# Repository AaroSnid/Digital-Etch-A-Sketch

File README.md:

# Digital Etch-A-Sketch

The **Digital Etch-A-Sketch** is a portable recreation of the classic Etch-A-Sketch drawing toy, built around an STM32 microcontroller, a 3.5" TFT display, and  rotary encoders for drawing cursor control. This project's main features are the rotary encoder cursor control, realistic screen erase gesture, and selectable drawing thickness.

> **Status:** Major Firmware Version Finalized
> **Hardware Version:** Rev1

---

## Features

- **Freehand Drawing**
  - Pixel-accurate cursor control
  - Trailless travel / eraser function
  - Selectable drawing thickness and brightness control

- **Physical Controls**
  - Two rotary encoders for X/Y movement
  - Encoder pushbuttons to for system setting selection

- **Shake to Erase**
  - Accelerometer detect motion for realistic screen erase gesture 

- **Portable & Low Power**
  - Powered by 2× AA batteries or by USB-C port

---

## Bill of Materials (Summary)

| Item            | Part Number        | Qty | Notes |
|-----------------|--------------------|-----|-------|
| MCU             | STM32L433CCT6      | 1   | Main controller |
| Display         | 3.5" ILI9488 SPI   | 1   | 3.5" display |
| QSPI Flash      | For future expansion | 1   | Reserved for future use |
| 3-axis Accelerometer      | LIS3DTHR        | 1   | 3-axis velocity sensor |
| Rotary Encoder  | PEC11R-4215F-S0024 | 2   | User input |
| Battery Holder  | Adafruit 4194      | 1   | 2× AA |

---

## Hardware Subsystems

### Power Supply

- **Part:** Adafruit 4194
- **Input:** 2 × AA batteries (2.2–3.2 V)
- **Output:** 3.0 V 
- **Max Load:** ~400 mA
- **Purpose:** Powers the entire system from AA cells

---

### Microcontroller

- **Part:** STM32L433CCT3 / STM32L433CCT6  
- **Clock:** 80 MHz (internal)
- **Memory:**  
  - 256 KB Flash  
  - 64 KB RAM  

**Key Peripherals**

| Function         | Peripheral | Notes |
|------------------|------------|-------|
| Display          | SPI3       | Half-duplex, optimized for fast updates |
| Accelerometer    | SPI2, EXTI | Full-duplex |
| Flash memory     | Quad-SPI   | Memory-mapped reads |
| Rotary Encoders  | TIM1&2, EXTI | QEI mode with interrupts |
| Debug            | SWD        | DIO, CLK, NRST |

---

### Display

- **Type:** 3.5" TFT Display
- **Controller:** ILI9488
- **Interface:** Dedicated 4-wire SPI
- **Power:** 3.3 V
- **Frame Buffer:** Embedded GRAM
- **Update Modes:** Full and partial refresh
The screen is mounted to the board using the female pin headers on either side. The touchscreen functionality of the screen is not used, so the touchscreen pins are not conected.

---

### Storage

- **Part:** For future expansion
- **Capacity:** Reserved for future use
- **Interface:** Quad SPI (if added later)
- **Purpose:**
  - Potential animation frame storage
  - Potential configuration data

---

### Motion Sensor

- **Part:** LIS3DTHR
- **Interface:** SPI
- **Capabilities:** 3-axis accelerometer
- **Usage:**
  - Detect shake gesture for screen erase
  - Uses interrupts for main motion detection
  - SPI available as fallback

---

### Rotary Encoders

- **Quantity:** 2
- **Part:** PEC11R-4215F-S0024
- **Purpose:**
  - X-axis and Y-axis cursor movement
  - UI interaction via push buttons

**Connections**
- A/B channels → Timer QEI inputs
- Buttons → EXTI interrupts
- Hardware Pull-ups (open-drain behavior)

---

## Firmware Architecture

### Overview

The firmware runs inside of a state machine, easily allowing for the same user inputs to be used for different purposes.
The main loop runs (per iteration) a check for the screen erase, handles state change, and then enters the state machine section for currently selected action.
An external driver is used for the ILI9488 display, all other firmware is made by me.

---

## Debug & Firmware Update

- **Interface:** SWD
- **Exposed Pins:**  
  - SWDIO  
  - SWCLK  
  - NRST  
  - VCC + GND

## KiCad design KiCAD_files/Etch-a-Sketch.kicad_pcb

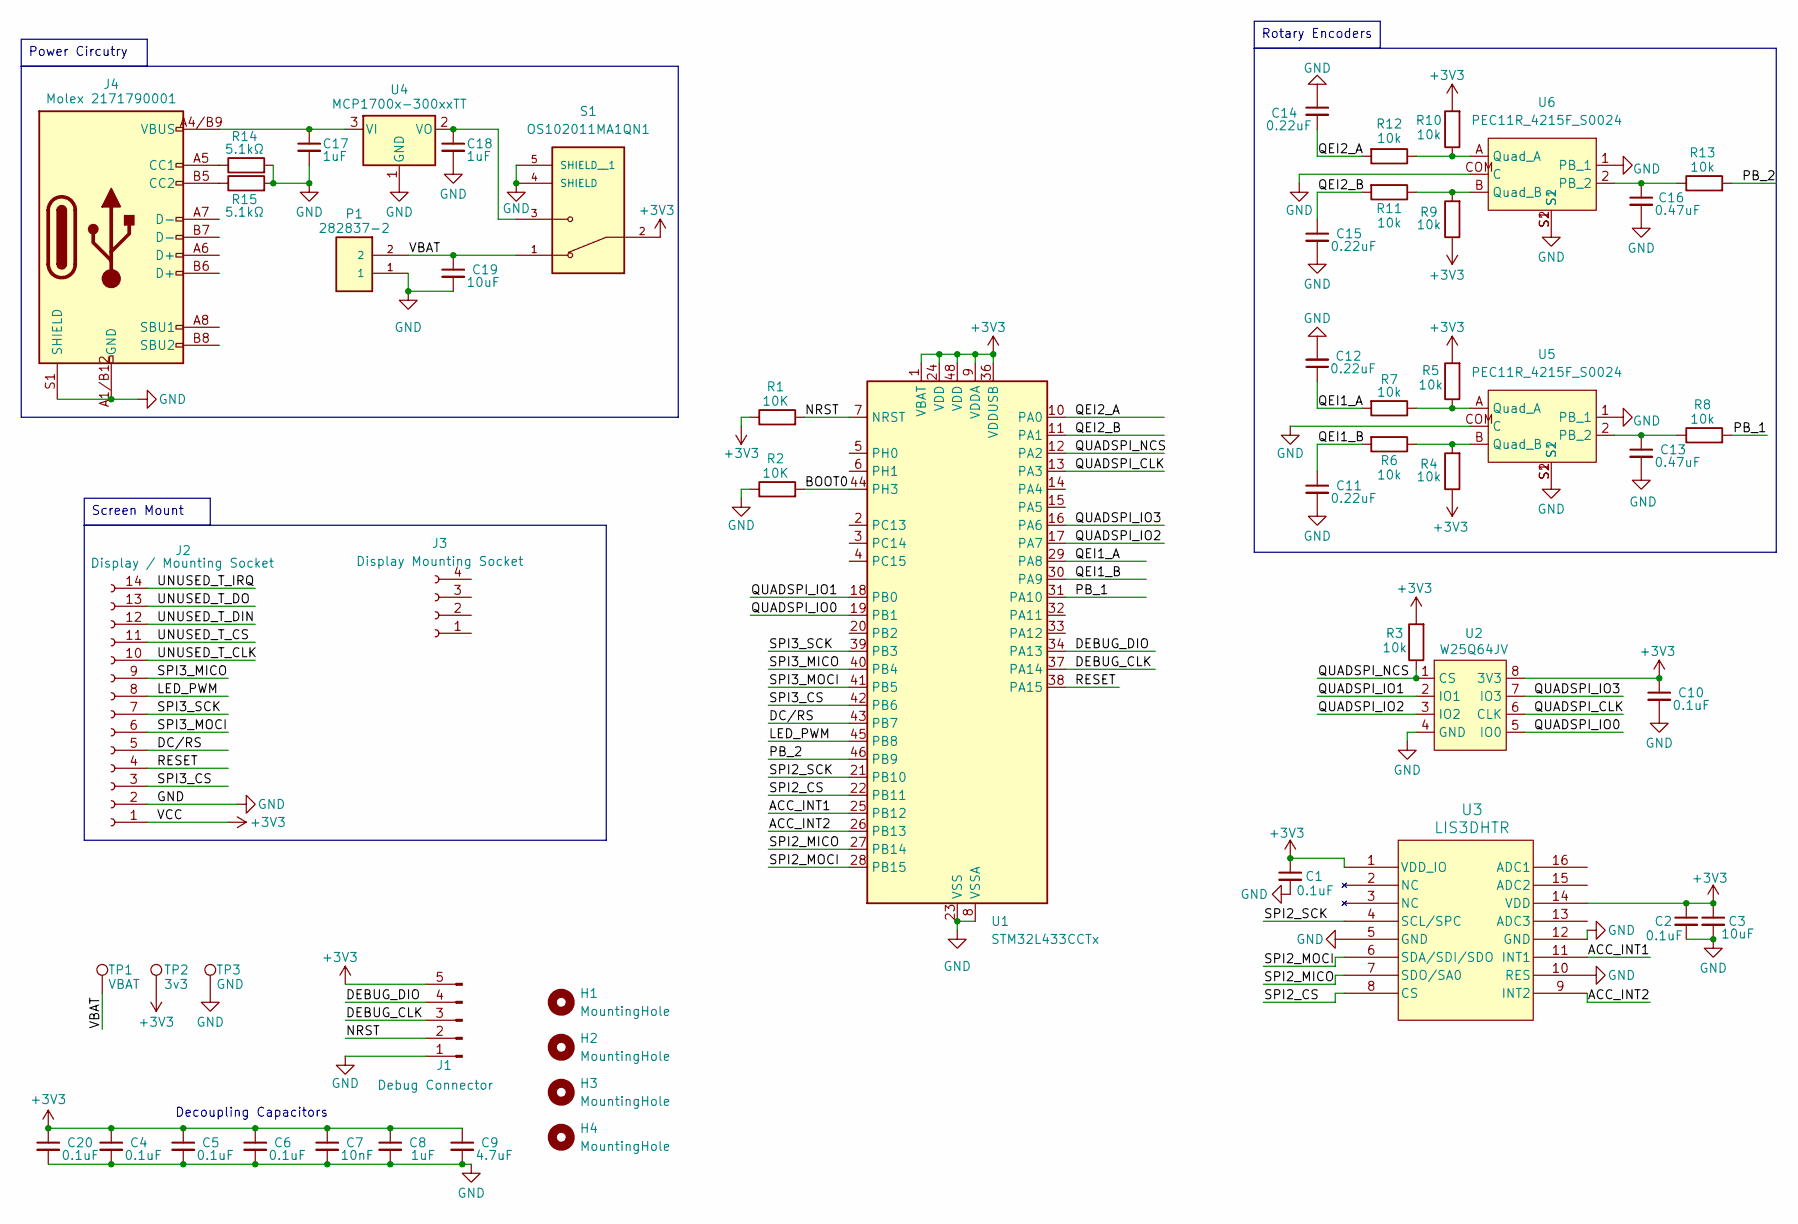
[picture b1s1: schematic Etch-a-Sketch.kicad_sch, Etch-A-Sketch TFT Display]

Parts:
C1, C2, C4, C5, C6, C10, C20: 0.1uF; C_0603_1608Metric
C3, C19: 10uF; C_0603_1608Metric
C7: 10nF; C_0603_1608Metric
C8, C17, C18: 1uF; C_0603_1608Metric
C9: 4.7uF; C_0603_1608Metric
C11, C12, C14, C15: 0.22uF; C_0603_1608Metric
C13, C16: 0.47uF; C_0603_1608Metric
H1, H2, H3, H4: MountingHole; ToolingHole_1.152mm
J1: Debug Connector; PinHeader_1x05_P2.54mm_Vertical
J2: Display / Mounting Socket; PinSocket_1x14_P2.54mm_Vertical
J3: Display Mounting Socket; PinSocket_1x04_P2.54mm_Vertical
J4: Molex 2171790001; 2171790001_MOL
P1: 282837-2; JST_PH_B2B-PH-K_1x02_P2.00mm_Vertical; PARTREV G3
R1, R2: 10K; R_0603_1608Metric
R3, R4, R5, R6, R7, R8, R9, R10, R11, R12, R13: 10k; R_0603_1608Metric
R14, R15: 5.1kΩ; R_0603_1608Metric
S1: OS102011MA1QN1; OS102011MA1QN1_CNK; PARTREV A
TP1: VBAT; TestPoint_Loop_D1.80mm_Drill1.0mm_Beaded
TP2: 3v3; TestPoint_Loop_D1.80mm_Drill1.0mm_Beaded
TP3: GND; TestPoint_Loop_D1.80mm_Drill1.0mm_Beaded
U1: STM32L433CCTx; LQFP-48_7x7mm_P0.5mm
U2: W25Q64JV; SOIC-8_5P28X5P28_WIN
U3: LIS3DHTR; LGA-16_3x3x1mm_STM
U4: MCP1700x-300xxTT; SOT-23
U5, U6: PEC11R_4215F_S0024; XDCR_PEC11R-4215F-S0024

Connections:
+3V3: C1.1, C2.1, C3.1, C4.1, C5.1, C6.1, C7.1, C8.1, C9.1, C10.1, C20.1, J1.5, J2.1, R1.1, R3.2, R4.1, R5.2, R9.1, R10.2, S1.2, TP2.1, U1.1 (VBAT), U1.9 (VDDA), U1.24 (VDD), U1.36 (VDDUSB), U1.48 (VDD), U2.8 (3V3), U3.1 (VDD_IO), U3.14 (VDD); also elsewhere on the board
/ACC_INT1: U1.25 (PB12), U3.11 (INT1)
/ACC_INT2: U1.26 (PB13), U3.9 (INT2)
/BOOT0: R2.2, U1.44 (PH3)
/DC/RS: J2.5, U1.43 (PB7)
/DEBUG_CLK: J1.3, U1.37 (PA14)
/DEBUG_DIO: J1.4, U1.34 (PA13)
/LED_PWM: J2.8, U1.45 (PB8)
/NRST: J1.2, R1.2, U1.7 (NRST)
/PB_1: R8.2, U1.31 (PA10)
/PB_2: R13.2, U1.46 (PB9)
/QEI1_A: C12.1, R7.2, U1.29 (PA8)
/QEI1_B: C11.1, R6.2, U1.30 (PA9)
/QEI2_A: C14.2, R12.2, U1.10 (PA0)
/QEI2_B: C15.1, R11.2, U1.11 (PA1)
/QUADSPI_CLK: U1.13 (PA3), U2.6 (CLK)
/QUADSPI_IO0: U1.19 (PB1), U2.5 (IO0)
/QUADSPI_IO1: U1.18 (PB0), U2.2 (IO1)
/QUADSPI_IO2: U1.17 (PA7), U2.3 (IO2)
/QUADSPI_IO3: U1.16 (PA6), U2.7 (IO3)
/QUADSPI_NCS: R3.1, U1.12 (PA2), U2.1 (CS)
/RESET: J2.4, U1.38 (PA15)
/SPI2_CS: U1.22 (PB11), U3.8 (CS)
/SPI2_MICO: U1.27 (PB14), U3.7 (SDO/SA0)
/SPI2_MOCI: U1.28 (PB15), U3.6 (SDA/SDI/SDO)
/SPI2_SCK: U1.21 (PB10), U3.4 (SCL/SPC)
/SPI3_CS: J2.3, U1.42 (PB6)
/SPI3_MICO: J2.9, U1.40 (PB4)
/SPI3_MOCI: J2.6, U1.41 (PB5)
/SPI3_SCK: J2.7, U1.39 (PB3)
/UNUSED_T_CLK: J2.10
/UNUSED_T_CS: J2.11
/UNUSED_T_DIN: J2.12
/UNUSED_T_DO: J2.13
/UNUSED_T_IRQ: J2.14
/VBAT: C19.1, P1.2, S1.1, TP1.1; also elsewhere on the board
GND: C1.2, C2.2, C3.2, C4.2, C5.2, C6.2, C7.2, C8.2, C9.2, C10.2, C11.2, C12.2, C13.2, C14.1, C15.2, C16.2, C17.2, C18.2, C19.2, C20.2, J1.1, J2.2, J4.A1/B12 (GND), J4.B1/A12 (GND), J4.S1 (SHIELD), P1.1, R2.1, R14.2, R15.2, S1.4 (SHIELD), S1.5 (SHIELD__1), TP3.1, U1.8 (VSSA), U1.23 (VSS), U1.35 (VSS), U1.47 (VSS), U2.4 (GND), U3.5 (GND), U3.10 (RES), U3.12 (GND), U4.1 (GND), U5.1 (PB_1), U5.COM (C), U5.S1, U5.S2, U6.1 (PB_1), U6.COM (C), U6.S1, U6.S2; also elsewhere on the board
unnamed: J4.A5 (CC1), R14.1
unnamed: J4.B5 (CC2), R15.1
unnamed: C17.1, J4.A4/B9 (VBUS), J4.B4/A9 (VBUS), U4.3 (VI)
unnamed: C18.1, S1.3, U4.2 (VO)
unnamed: C13.1, R8.1, U5.2 (PB_2)
unnamed: R5.1, R7.1, U5.A (Quad_A)
unnamed: R4.2, R6.1, U5.B (Quad_B)
unnamed: C16.1, R13.1, U6.2 (PB_2)
unnamed: R10.1, R12.1, U6.A (Quad_A)
unnamed: R9.2, R11.1, U6.B (Quad_B)

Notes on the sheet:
Decoupling Capacitors
Screen Mount
Rotary Encoders
Power Circutry

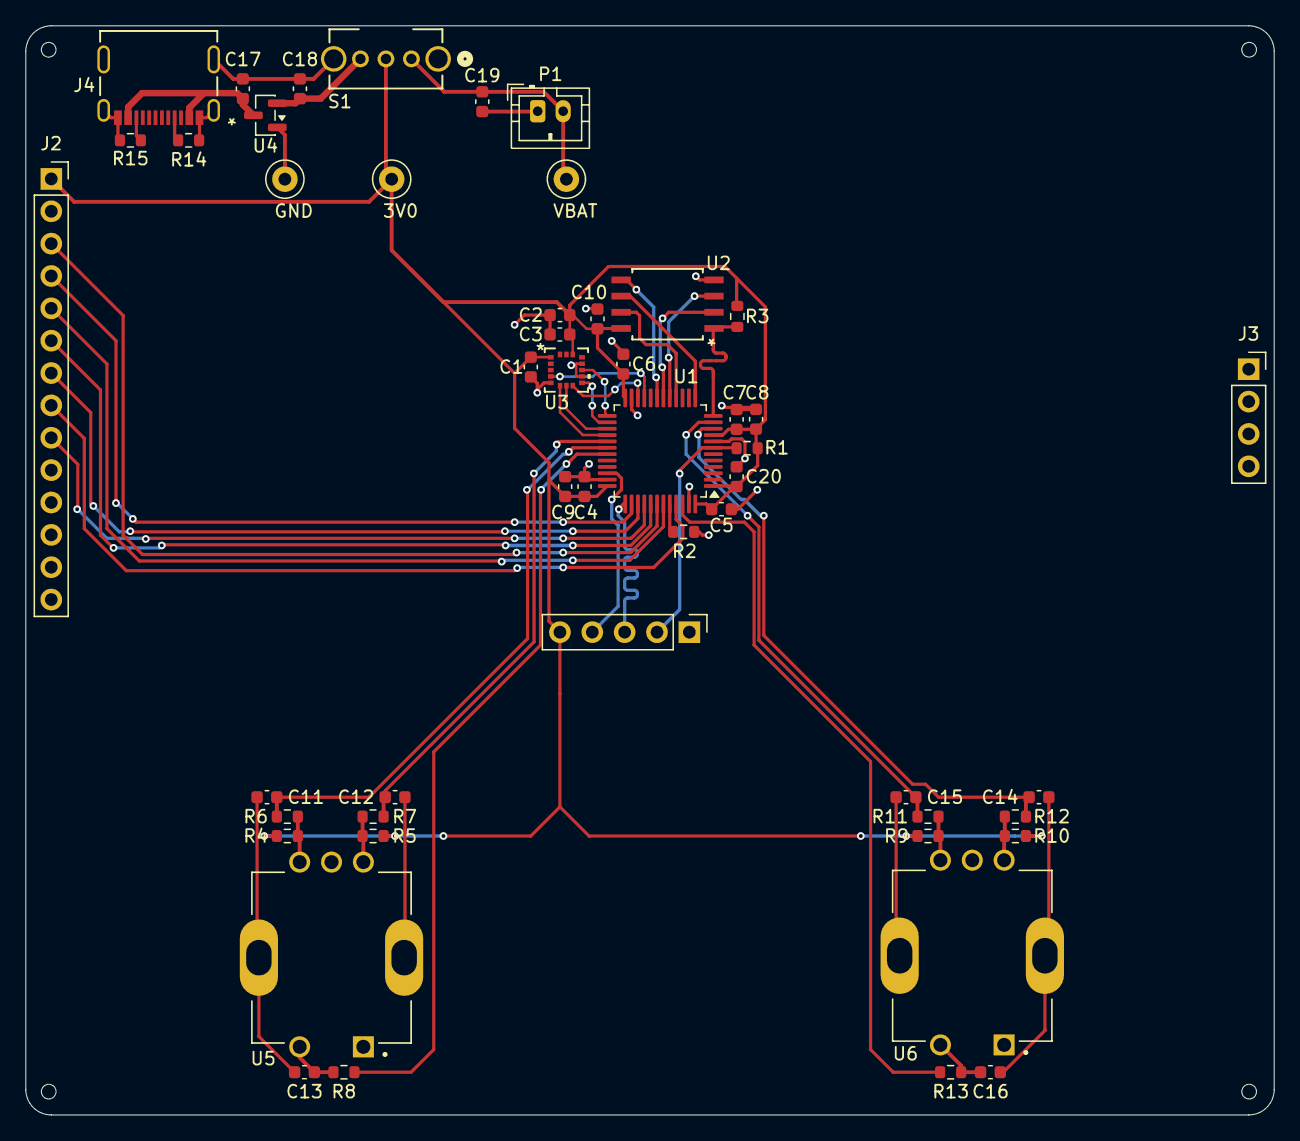
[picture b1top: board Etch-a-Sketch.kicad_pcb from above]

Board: 2 copper layers, 98.0 x 85.5 mm, 54 parts (0 on the bottom side), 42 nets.

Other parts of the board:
3V0: 3v3; TestPoint_Loop_D1.80mm_Drill1.0mm_Beaded
GND: GND; TestPoint_Loop_D1.80mm_Drill1.0mm_Beaded
VBAT: VBAT; TestPoint_Loop_D1.80mm_Drill1.0mm_Beaded

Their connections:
+3V3: 3V0.1; also elsewhere on the board
/VBAT: VBAT.1; also elsewhere on the board
GND: GND.1; also elsewhere on the board

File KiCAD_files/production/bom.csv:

Designator,Footprint,Quantity,Value,LCSC Part #
"C1, C10, C20, C3, C4, C5, C6",0603,7,0.1uF,
"C11, C12, C14, C15",0603,4,0.22uF,
"C13, C16",0603,2,0.47uF,
"C17, C18, C8",0603,3,1uF,
"C19, C2",0603,2,10uF,
C7,0603,1,10nF,
C9,0603,1,4.7uF,
J1,PinHeader_1x05_P2.54mm_Vertical,1,Debug Connector,
J2,PinSocket_1x14_P2.54mm_Vertical,1,Display / Mounting Socket,
J3,PinSocket_1x04_P2.54mm_Vertical,1,Display Mounting Socket,
J4,2171790001_MOL,1,Molex 2171790001,
"R1, R10, R11, R12, R13, R2, R3, R4, R5, R6, R7, R8, R9",0603,13,10K,
"R14, R15",0603,2,5.1kΩ,
S1,OS102011MA1QN1_CNK,1,OS102011MA1QN1,
U1,LQFP-48_7x7mm_P0.5mm,1,STM32L433CCTx,
U2,SOIC-8_5P28X5P28_WIN,1,W25Q64JV,
U3,LGA-12_STM,1,LIS2DH12TR,
U4,SOT-23,1,MCP1700x-300xxTT,
"U5, U6",XDCR_PEC11R-4215F-S0024,2,PEC11R_4215F_S0024,

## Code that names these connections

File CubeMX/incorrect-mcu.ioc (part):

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Mcu.Name=STM32L433C(B-C)Ux
Mcu.Package=UFQFPN48
Mcu.UserName=STM32L433CCUx
PA0.GPIOParameters=GPIO_PuPd
PA0.GPIO_PuPd=GPIO_PULLUP
PA0.Signal=S_TIM2_CH1
PA1.GPIOParameters=GPIO_PuPd
PA1.GPIO_PuPd=GPIO_PULLUP
PA1.Signal=S_TIM2_CH2
PA10.GPIOParameters=GPIO_Label
PA10.GPIO_Label=EXTI_PB_1
PA10.Signal=GPXTI10
PA15\ (JTDI).Signal=GPIO_Output
PA2.Mode=Single Bank 1
PA2.Signal=QUADSPI_BK1_NCS
PA3.Mode=Single Bank 1
PA3.Signal=QUADSPI_CLK
PA6.Mode=Single Bank 1
PA6.Signal=QUADSPI_BK1_IO3
PA7.Mode=Single Bank 1
PA7.Signal=QUADSPI_BK1_IO2
PA8.GPIOParameters=GPIO_PuPd
PA8.GPIO_PuPd=GPIO_PULLUP
PA8.Signal=S_TIM1_CH1
PA9.GPIOParameters=GPIO_PuPd
PA9.GPIO_PuPd=GPIO_PULLUP
PA9.Signal=S_TIM1_CH2
PB0.Mode=Single Bank 1
PB0.Signal=QUADSPI_BK1_IO1
PB1.Mode=Single Bank 1
PB1.Signal=QUADSPI_BK1_IO0
PB10.Mode=Full_Duplex_Master
PB10.Signal=SPI2_SCK
PB11.GPIOParameters=GPIO_Label
PB11.GPIO_Label=SPI2_CS
PB11.Signal=GPIO_Output
PB12.GPIOParameters=GPIO_Label
PB12.GPIO_Label=EXTI_IMU_INT2
PB12.Signal=GPXTI12
PB13.GPIOParameters=GPIO_Label
PB13.GPIO_Label=EXTI_IMU_INT1
PB13.Signal=GPXTI13
PB14.Mode=Full_Duplex_Master
PB14.Signal=SPI2_MISO
PB15.Mode=Full_Duplex_Master
PB15.Signal=SPI2_MOSI
PB3\ (JTDO-TRACESWO).Mode=Full_Duplex_Master
PB3\ (JTDO-TRACESWO).Signal=SPI3_SCK
PB4\ (NJTRST).Mode=Full_Duplex_Master
PB4\ (NJTRST).Signal=SPI3_MISO
PB5.Mode=Full_Duplex_Master
PB5.Signal=SPI3_MOSI
PB6.GPIOParameters=GPIO_Label
PB6.GPIO_Label=SPI3_CS
PB6.Signal=GPIO_Output
PB7.Signal=GPIO_Output
PB8.Signal=S_TIM16_CH1
PB9.GPIOParameters=GPIO_Label
PB9.GPIO_Label=EXTI_TIM2
PB9.Signal=GPXTI9
RCC.HSE_VALUE=8000000
board=custom

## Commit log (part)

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2025-11-07 Finish schematic Rev1 and begin layout
2025-11-14 Add footprints and 3D models, initial component layout, hardware improvements
2025-11-17 Initial PCB Layout
2025-11-18 PCB layout draft and clean files
2025-12-09 Final KiCAD updates, and begin driver developpment
2025-12-10 ICM-42688 Driver Development
2025-12-11 Add driver calibration and style fix
2025-12-11 Add ICM-42688-P Driver
2025-12-16 Add ILI9488 Driver and Basic Functionality
2025-12-18 Configure buttons and drawing on edge fix
2025-12-19 Add initial project desctiption
2025-12-22 Initial IMU implementation
2025-12-23 Initial Rev1 Changes, including
    Mounting holes
    Switch to choose backlight reference to replace jumper resistors
    Pull ups/downs for NRST and BOOT0
    Move the debug connector location
    Relabel passive components
    Add jumper resistors to remove power from ICs
2025-12-30 Move screen erase logic to main loop
2026-01-05 Add Board Revision 1
2026-04-30 Update Schematic to Rev1
2026-05-01 Initial Rev1 PCB Layout
2026-05-08 Change Accelerometer IC
2026-05-16 Send Rev1 Out For Production
2026-06-01 Set Up STM32 Development Files
2026-06-02 Transfer Prototype Code to New Version
2026-06-04 Add New Revision Media to Project
2026-06-12 Set Up and Configure Driver Files
2026-06-13 Add Accelerometer config
2026-06-13 Integrate Accelerometer to Project
2026-06-17 Add debug launch.json file
2026-06-18 Run Rev1 Board!
2026-06-20 Transition System States to Use an Enum
2026-06-26 Modify Project Scope in README
2026-06-29 Add Line Thickness Adjustment
2026-06-30 Add Pick-Up&Place/Erase Cursor Feature
